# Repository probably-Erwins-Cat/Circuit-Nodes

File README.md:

# Circuit Nodes - Modular Electronics Building Blocks

Circuit Nodes is an educational tool shared under CC BY-NC-SA 4.0 to help students understand electronic circuits by physically building them.
Each module consists of a small PCB mounted on a 3D-printed base with puzzle-like notches, allowing users to create circuits in a grid-based structure. 
The PCBs include simple circuit elements such as resistors, capacitors, wire traces, switches, LEDs, lamps, and voltage or current measurement points, with their schematic representations printed directly on them. 
Magnetic connectors enable both physical attachment and electrical connection.

This system provides a low-cost entry point into electronics education while remaining scalable. 
By starting with basic components and expanding into more complex circuits, learners of all levels can benefit. 
The pedagogical value lies in reinforcing the connection between abstract circuit diagrams and tangible, working implementations, 
making theoretical concepts easier to grasp through hands-on experimentation.

---

## 📖 **[→ EXPLORE THE FULL DOCUMENTATION](https://probably-erwins-cat.github.io/Circuit-Nodes/)**

Complete guides, examples, research insights, and best practices are available in our **comprehensive GitHub Pages site**:

| Chapter | Link |
|---------|------|
| **Introduction** | https://probably-erwins-cat.github.io/Circuit-Nodes/introduction |
| **Getting Started** | https://probably-erwins-cat.github.io/Circuit-Nodes/getting-started |
| **Printable Bases** | https://probably-erwins-cat.github.io/Circuit-Nodes/printable-bases |
| **Assembly Instructions** | https://probably-erwins-cat.github.io/Circuit-Nodes/assembly-instructions |
| **Component Guide** | https://probably-erwins-cat.github.io/Circuit-Nodes/component-guide |
| **Sourcing & Manufacturing** | https://probably-erwins-cat.github.io/Circuit-Nodes/sourcing-manufacturing |
| **Getting Started** | https://probably-erwins-cat.github.io/Circuit-Nodes/getting-started |

# Features

*If you are an educator or represent a school interested in testing Circuit
Nodes, I can provide kits for evaluation and classroom use. Please reach out for
more details, see below*

-   Modular Design: 40x40mm PCBs mounted on 3D-printed bases with interlocking
    puzzle-like edges.
-   Hands-on Learning: Users assemble working circuits based on schematic
    diagrams.
-   Magnetic Connectors: Ensure secure physical and electrical connections.
-   Visual Representation: Each PCB features the corresponding circuit schematic
    for intuitive learning.
-   Expandable: Additional modules with more components can be designed and
    added.
-   Low Cost & Scalable: An affordable introduction to electronics that can be
    expanded as needed.

-   Pre-Assembled Kits Available: If the initial effort of manufacturing and
    assembling the components seems too high, I can provide ready-made circuit
    kits to make getting started easier.

# Getting Started, Assembly Instructions

- Refer to the repository contents below for a dedicated list and example circuits. 
- Plan what puzzle pieces you need and how many. An entry electronics kit for school settings needs less than 40 to cover most grounds.
- Download the necessary Gerber files for the circuits or kits you want to build from this repository.
- Manufacture the PCBs using your preferred(accessible) PCB fabrication service. 
  - Talk to the manufacturer if they can provide discounts for educational purpose. 
  - I recommend black background/solder mask and white silkscreen print. From my experience, this combination is the most durable combination.

-   **Decide which style of the 3D printable base you prefer for your scenario**:
    -  PCBs support screws of size M2, M2.3, and M2.6 self-tapping, as well as M2, M2.5 and M3 normal screws in combination with heat inserts.
        -   *Self-Tapping*: I recommend **M2 self-tapping and countersunk**
            screws. They provide the cleanest look, do not require additional
            assembly steps and auto-align the PCBs.
            Self-tapping screws, **can carve multiple threads when reinserting**, limited number of reuse of printable base.
        -   *Heat insert version*: Heat inserts provide **more durable and reliable way** for normal M2 and M2.5, 
            but requires time-consuming melting in the heat inserts with a solder iron or heat insert press.
    -   **Base Bottom Style**:
        -   The *magnetic bottom* base has highest build plate adhesion and allows for installing neodymium magnet, 
            so that the part can be attached to a magnetic surface. The internal height for components will be reduced by approx 3mm down to approx 16mm.
            **This makes a good teacher set for blackboards and whiteboards**
        -   The *skeletonized* one allows to look inside, but prevents curious
            fingers to get inside to accidentally break parts but allows exploring how
            components look in real life.
        -   The *open bottom* uses the least amount of material, is the fastest to
            print and, in case of a damaged component, the bottom side can be
            reached with a solder iron for *repair without disassembly*.            

-   **Before you go mass printing the base parts**, check which tolerance class,
    0.15mm and 0.2mm, suits your printer capabilities. 
    - The puzzle pieces should fit in together without a lot of wiggle room and without a lot of friction.
    - Smallest tolerance is preferred for best alignment of the parts.
-   Solder the component of the schematic of the PCB onto it first.
-   Assemble the puzzle pieces by placing the magnetic connectors in the pockets
    for the dedicated PCBs first. Slots without electrical connection stay     empty.
-   Place the PCB on top of the pins of the magnetic connectors and screw in
    four screws into the base. Screws should auto-center the PCB on the base.
-   Solder the magnetic connectors to the PCB.
-   Start building and experimenting with different circuit configurations!

You can also contact me for production and sale, I stock the puzzle pieces in my inventory and do quality checks including all other parts for assembly.

# Contributing

Contributions are welcome! Feel free to submit pull requests with new module
designs, improvements, or documentation updates. If you are a teacher and would
like to see specific schematics that align with your curriculum, but lack the
KiCAD skills to design them, I am happy to assist with the schematic design
process. Just reach out with your requirements, and I can help bring them to
life for your students.

Before submitting files, read [CONTRIBUTING.md](CONTRIBUTING.md). It explains
how contributed designs remain available for future Circuit Nodes kits while
contributors keep ownership of their work.

# Contact

For questions or collaboration, please open an discussion or reach out to me.

# DOI

# License

Circuit Nodes material is offered under **CC BY-NC-SA 4.0** (Creative Commons
Attribution-NonCommercial-ShareAlike 4.0 International) where the project holds
the necessary rights. You may use the design files to make your own Circuit
Nodes for noncommercial purposes. Schools may be able to commission ordinary
fabrication and assembly services for that use. The public license does not
permit use of licensed material primarily for commercial advantage. The project
creator retains the right to manufacture and sell products based on material
for which they hold the necessary rights. See
[LICENSING.md](LICENSING.md) for scope and
[LICENSE](LICENSE) for the full license.

---

## 📚 Citation & Research

This project is supported by peer-reviewed research published in **Physics Education**:

**Kubitschke, H., Hennig, F., Gleichmann, J., Schnauß, J., & Bitzenbauer, P. (2024).** 
*Modular 3D-printed Circuit Nodes for low-cost and hands-on Electricity Education.* 
Physics Education, 61(1), 015010.
**DOI**: [10.1088/1361-6552/ae1abd](https://doi.org/10.1088/1361-6552/ae1abd)

The paper includes:
- Educational design principles and cognitive load theory
- Technical specifications and cost analysis
- Teacher evaluation and feedback from 8 German secondary school physics teachers
- Learning outcome research and student perception studies

[Read the research publication](https://doi.org/10.1088/1361-6552/ae1abd) for detailed insights.

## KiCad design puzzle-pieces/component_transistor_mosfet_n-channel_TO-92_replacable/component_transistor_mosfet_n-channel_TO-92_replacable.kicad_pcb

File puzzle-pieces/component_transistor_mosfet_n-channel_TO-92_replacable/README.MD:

# Replaceable N-channel MOSFET (TO-92)

This node demonstrates how a gate voltage controls current through a transistor.

**The MOSFET is unprotected, but replaceable using the precision socket.** There is no built-in protection against incorrect connections, excessive gate voltage, or excessive current. The socket makes it easy to replace a damaged MOSFET or compare different types; it does not provide electrical protection.

## Connections and classroom use

| Terminal | Function |
| --- | --- |
| G: gate | Controls conduction through its voltage relative to the source |
| D: drain | Connects to the load; the other side of the load connects to the positive supply |
| S: source | Connects to the supply return in a low-side switching experiment |

At approximately zero gate-to-source voltage, the transistor is off in the normal drain-to-source direction. Increasing gate voltage allows current to flow. **Threshold voltage marks the beginning of conduction, not full turn-on.** These parts are useful for small-load experiments around a 5 V gate drive; do not assume reliable full turn-on at 3.3 V.

- Measure load current as gate voltage changes.
- Compare voltage-driven gate control with the base current of an NPN transistor.
- Observe that a disconnected gate can retain charge. An external gate-to-source pull-down resistor, for example 100 kΩ, gives a defined off state.
- Investigate the internal body diode: an off MOSFET does not block current equally in both directions.

## Suggested parts and usage

The three contacts have 2.54 mm spacing. Solder a precision socket onto the diagram side and plug the MOSFET into it, as shown above. This allows a damaged MOSFET to be replaced or different types to be compared. A matching MOSFET can also be soldered directly into the same pads.

Use a TO-92 MOSFET with **1 = source, 2 = gate, 3 = drain (S-G-D)**. Wide in-line leads fit the socket pitch; closely spaced leads can be gently spread beforehand.

| MOSFET | Maximum drain-source voltage | Pin order, flat face toward you and leads pointing down |
| --- | --- | --- |
| 2N7000 | 60 V | S-G-D |
| TN0606N3-G | 60 V | S-G-D |
| VN0106N3-G | 60 V | S-G-D |
| TN0610N3-G | 100 V | S-G-D |
| VN10KN3-G | 60 V | S-G-D |

These are pin-compatible options, but their switching characteristics and current limits differ. Check the exact manufacturer's datasheet before fitting a replacement. The drain-source rating is not the permissible gate voltage.

**Insert the MOSFET with each lead connected to the corresponding S, G, or D terminal.** Disconnect power before replacing it.

## Practical notes

This node has no built-in gate protection, pull-down resistor, load-current limiter, or flyback diode. Use an external resistor/current limit for the load and a flyback diode for inductive loads.

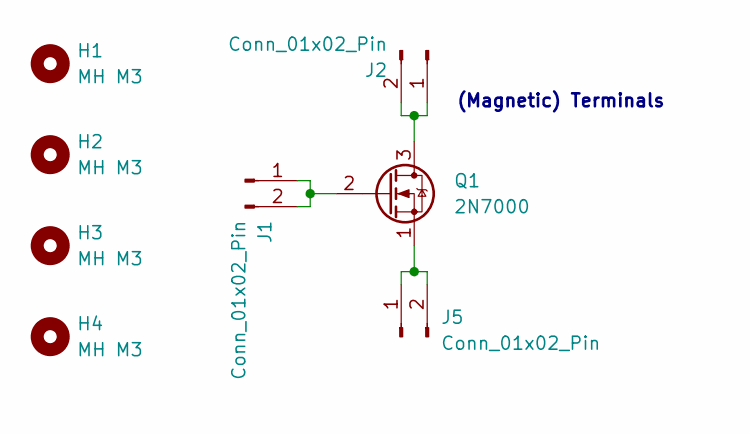
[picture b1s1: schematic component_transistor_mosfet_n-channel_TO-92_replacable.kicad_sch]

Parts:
H1, H2, H3, H4: MH M3; MountingHole_3.0mm_M3_tight
J1, J2, J5: Conn_01x02_Pin; Magnetic_Connector_1x02_P2.5mm_Horizontal_round-ears
Q1: 2N7000; HDR-TH_3P-P2.54-V-F-3

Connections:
Leitung1: J5.1, J5.2, Q1.1 (S)
unnamed: J1.1, J1.2, Q1.2 (G)
unnamed: J2.1, J2.2, Q1.3 (D)

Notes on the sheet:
(Magnetic) Terminals

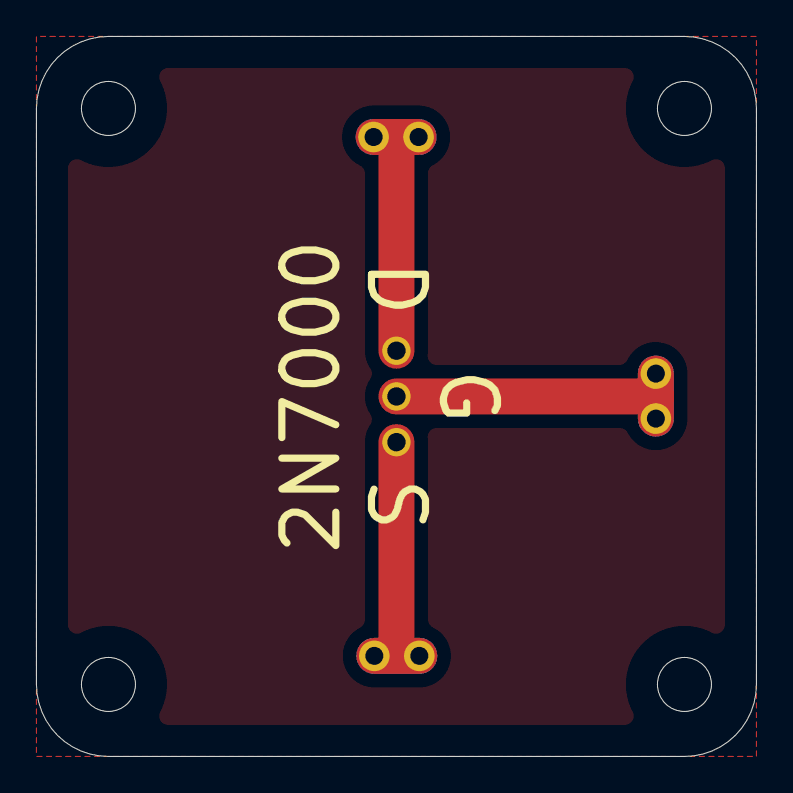
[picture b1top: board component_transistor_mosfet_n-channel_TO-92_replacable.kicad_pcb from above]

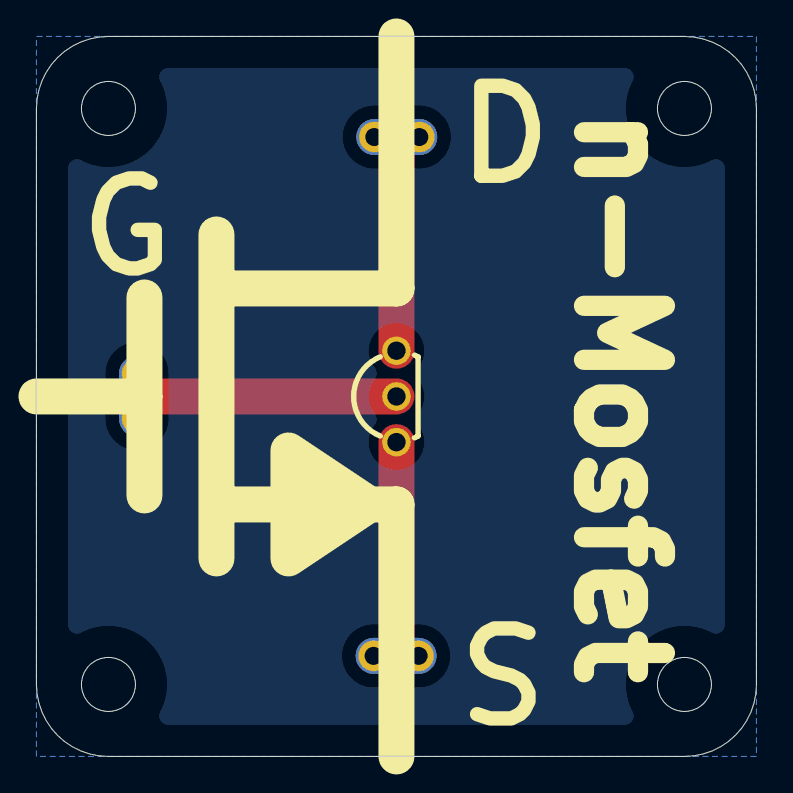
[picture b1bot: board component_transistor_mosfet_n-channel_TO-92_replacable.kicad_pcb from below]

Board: 2 copper layers, 40.0 x 40.0 mm, 8 parts (5 on the bottom side), 3 nets.

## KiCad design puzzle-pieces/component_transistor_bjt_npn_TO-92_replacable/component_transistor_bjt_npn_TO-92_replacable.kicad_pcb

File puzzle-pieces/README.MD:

# Circuit Nodes Puzzle Pieces

All Circuit Nodes puzzle pieces are collected and constantly updated here. Each piece represents a specific circuit component or connection type, named according to their schematic symbols rather than specific component numbers. For example, the folder for an n-channel MOSFET will contain compatible part numbers like the 2N7000.

## Design Standard

All puzzle pieces follow a consistent design template to ensure they work together seamlessly:

- **Physical dimensions**: 40×40 mm square outline with 4 mm radius corners
- **Mounting**: Four M3-compatible screw holes in the corners (2.9–3.0 mm diameter, 4 mm from edges)
- **Visual style**: 2 mm thick pictogram lines with rounded edges where possible
- **Electrical layout**: Copper pour kept at least 2 mm from board edges and not connected to GND or power supply
- **Connector interface**: Integrated magnetic pogo connectors (see the dedicated pogo-connector folder)

## Board-to-Board Connectors

All pieces are designed for integrated magnetic pogo connectors. The layout and spacing of each puzzle piece are carefully matched to these connectors for reliable, automatic alignment when pieces are joined.

## Complete Catalog

| Name | Image |
|------|-------|
| [breadboard_grid-2.54mm_1x1](breadboard_grid-2.54mm_1x1) |  |
| [breadboard_grid-2.54mm_1x2](breadboard_grid-2.54mm_1x2) |  |
| [breadboard_grid-2.54mm_2x2](breadboard_grid-2.54mm_2x2) |  |
| [component_capacitor-polarized_ruggedized](component_capacitor-polarized_ruggedized) |  |
| [component_capacitor-polarized_ruggedized_replacable](component_capacitor-polarized_ruggedized_replacable) |  |
| [component_capacitor-unpolarized-MLCC_SMT](component_capacitor-unpolarized-MLCC_SMT) |  |
| [component_charge-pump-inverter](component_charge-pump-inverter) |  |
| [component_diode_general_silicon](component_diode_general_silicon) |  |
| [component_diode_zener](component_diode_zener) |  |
| [component_fuse-PolyFuse](component_fuse-PolyFuse) |  |
| [component_inductance_THT](component_inductance_THT) |  |
| [component_lamp-E10_screw-socket](component_lamp-E10_screw-socket) |  |
| [component_lamp-E10_THT](component_lamp-E10_THT) |  |
| [component_lamp-LED-module_ruggedized](component_lamp-LED-module_ruggedized) |  |
| [component_LED_replacable](component_LED_replacable) |  |
| [component_LED_THT](component_LED_THT) |  |
| [component_motor-with-propeller](component_motor-with-propeller) |  |
| [component_potentiometer_high-power](component_potentiometer_high-power) |  |
| [component_potentiometer_slider_screw-mounted](component_potentiometer_slider_screw-mounted) |  |
| [component_potentiometer_slider_THT](component_potentiometer_slider_THT) |  |
| [component_resistor_SMT](component_resistor_SMT) |  |
| [component_resistor_SMT_top-mount](component_resistor_SMT_top-mount) |  |
| [component_resistor_SMT_with-printed-value](component_resistor_SMT_with-printed-value) |  |
| [component_resistor_THT_3W](component_resistor_THT_3W) |  |
| [component_resistor_THT_3W_with-printed-value](component_resistor_THT_3W_with-printed-value) |  |
| [component_switch-micro-Normally-Closed_THT](component_switch-micro-Normally-Closed_THT) |  |
| [component_switch-micro-Normally-Open_THT](component_switch-micro-Normally-Open_THT) |  |
| [component_switch-On-OFF_THT](component_switch-On-OFF_THT) |  |
| [component_switch-On1-OFF-On2_THT](component_switch-On1-OFF-On2_THT) |  |
| [component_switch-On1-On2_THT](component_switch-On1-On2_THT) |  |
| [component_switch-tactile-Normally-Open_THT](component_switch-tactile-Normally-Open_THT) |  |
| [component_transistor_bjt_npn_TO-92_replacable](component_transistor_bjt_npn_TO-92_replacable) |  |
| [component_transistor_mosfet_n-channel_ruggedized](component_transistor_mosfet_n-channel_ruggedized) |  |
| [component_transistor_mosfet_n-channel_TO-92_replacable](component_transistor_mosfet_n-channel_TO-92_replacable) |  |
| [end-node-double_AC](end-node-double_AC) |  |
| [end-node-double_blank](end-node-double_blank) |  |
| [end-node-double_current](end-node-double_current) |  |
| [end-node-double_plus-minus](end-node-double_plus-minus) |  |
| [end-node-double_plus-minus_with-protection](end-node-double_plus-minus_with-protection) |  |
| [end-node-double_plus-minus_with-USB-PD](end-node-double_plus-minus_with-USB-PD) |  |
| [end-node-single_blank](end-node-single_blank) |  |
| [end-node-single_minus](end-node-single_minus) |  |
| [end-node-single_plus](end-node-single_plus) |  |
| [wire-angle_blank](wire-angle_blank) |  |
| [wire-angle_node-voltage](wire-angle_node-voltage) |  |
| [wire-bridge_blank](wire-bridge_blank) |  |
| [wire-straight_blank](wire-straight_blank) |  |
| [wire-straight_node-voltage](wire-straight_node-voltage) |  |
| [wire-T-crossing_blank](wire-T-crossing_blank) |  |
| [wire-T-crossing_node-voltage](wire-T-crossing_node-voltage) |  |
| [wire-two-angles_blank](wire-two-angles_blank) |  |
| [wire-X-crossing_blank](wire-X-crossing_blank) |  |
| [wire-X-crossing_node-voltage](wire-X-crossing_node-voltage) |  |

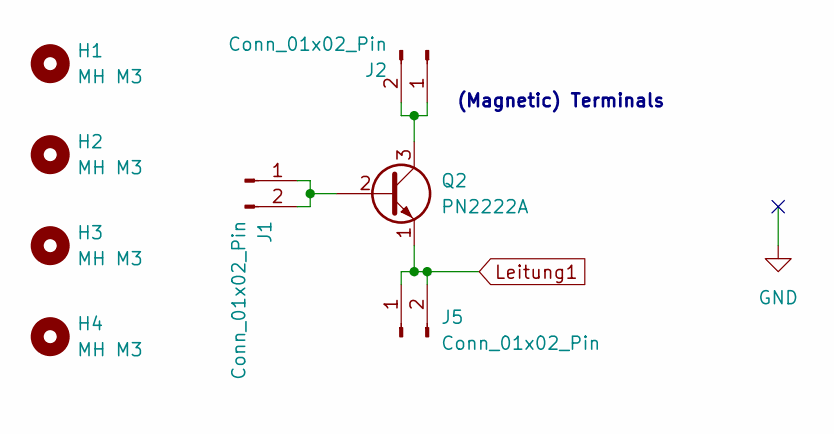
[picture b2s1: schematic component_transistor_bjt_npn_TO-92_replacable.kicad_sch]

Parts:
H1, H2, H3, H4: MH M3; MountingHole_3.0mm_M3_tight
J1, J2, J5: Conn_01x02_Pin; Magnetic_Connector_1x02_P2.5mm_Horizontal_round-ears
Q2: PN2222A; HDR-TH_3P-P2.54-V-F-3

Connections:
Leitung1: J5.1, J5.2, Q2.1 (E)
unnamed: J1.1, J1.2, Q2.2 (B)
unnamed: J2.1, J2.2, Q2.3 (C)

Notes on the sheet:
(Magnetic) Terminals

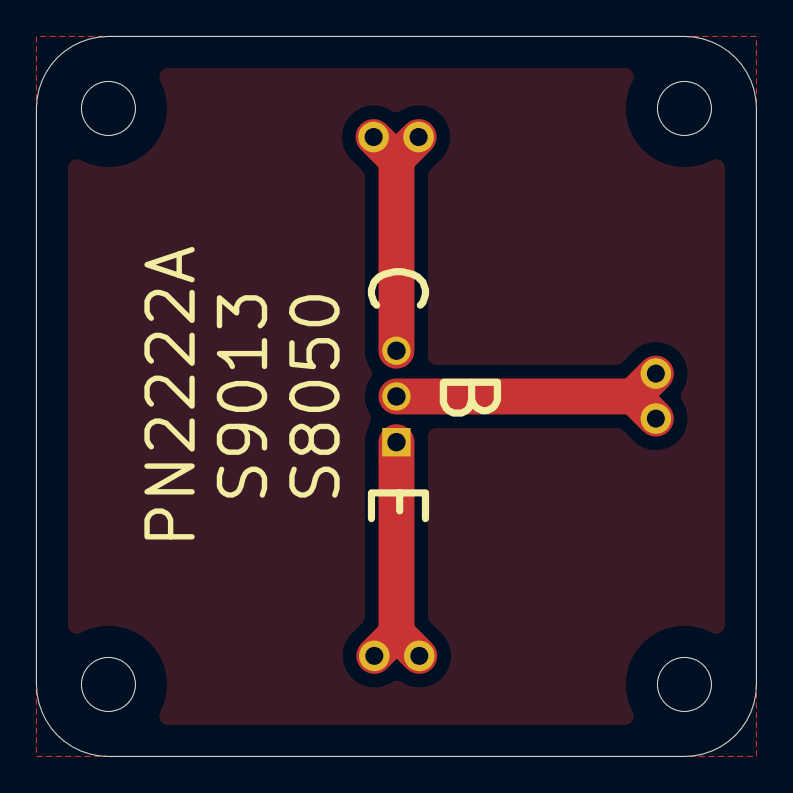
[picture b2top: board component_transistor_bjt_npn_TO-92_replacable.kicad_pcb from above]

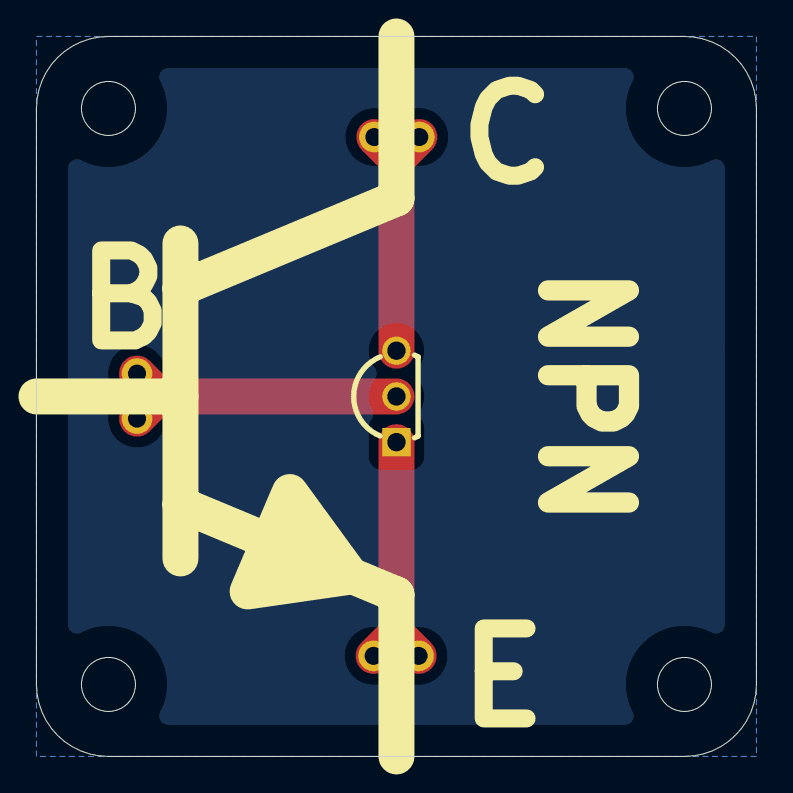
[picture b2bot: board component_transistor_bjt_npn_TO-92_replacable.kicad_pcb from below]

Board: 2 copper layers, 40.0 x 40.0 mm, 8 parts (5 on the bottom side), 3 nets.

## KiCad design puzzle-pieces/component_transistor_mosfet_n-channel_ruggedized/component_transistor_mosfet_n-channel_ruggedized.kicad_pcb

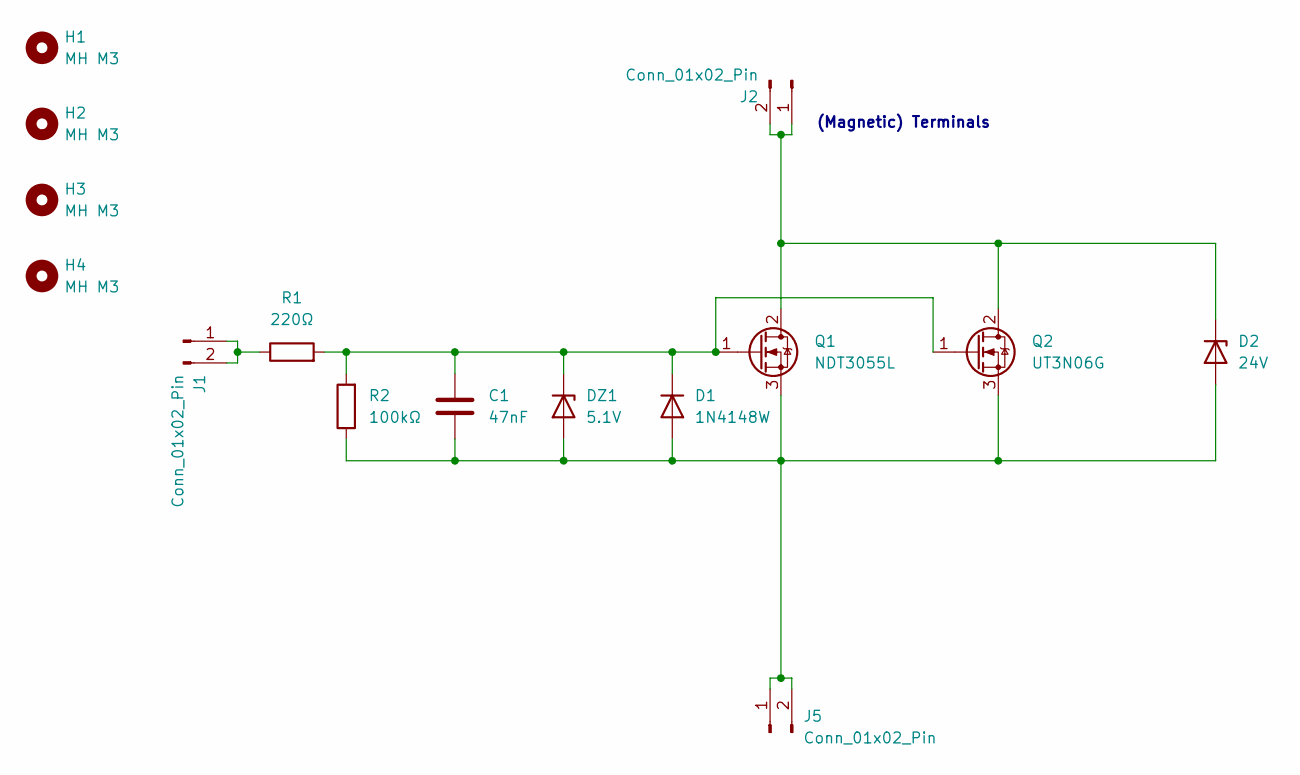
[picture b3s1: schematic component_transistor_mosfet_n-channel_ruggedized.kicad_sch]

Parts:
C1: 47nF; C_1206_3216Metric_Pad1.33x1.80mm_HandSolder; LCSC C303962
D1: 1N4148W; Nexperia_CFP3_SOD-123W; LCSC C81598
D2: 24V; D_SMA; LCSC C155317
DZ1: 5.1V; Nexperia_CFP3_SOD-123W; LCSC C2827905
H1, H2, H3, H4: MH M3; MountingHole_3.0mm_M3_tight
J1, J2, J5: Conn_01x02_Pin; Magnetic_Connector_1x02_P2.5mm_Horizontal_round-ears
Q1: NDT3055L; SOT-223-3_TabPin2; LCSC C5354979
Q2: UT3N06G; SOT-89-3_Handsoldering; LCSC C127044
R1: 220Ω; R_1206_3216Metric_Pad1.30x1.75mm_HandSolder; LCSC C17957
R2: 100kΩ; R_1206_3216Metric_Pad1.30x1.75mm_HandSolder; LCSC C17900

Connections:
unnamed: C1.2, D1.2 (A), D2.2 (A), DZ1.2 (A), J5.1, J5.2, Q1.3 (S), Q2.3 (S), R2.1
unnamed: C1.1, D1.1 (K), DZ1.1 (K), Q1.1 (G), Q2.1 (G), R1.2, R2.2
unnamed: D2.1 (K), J2.1, J2.2, Q1.2 (D), Q2.2 (D)
unnamed: J1.1, J1.2, R1.1

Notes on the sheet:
(Magnetic) Terminals

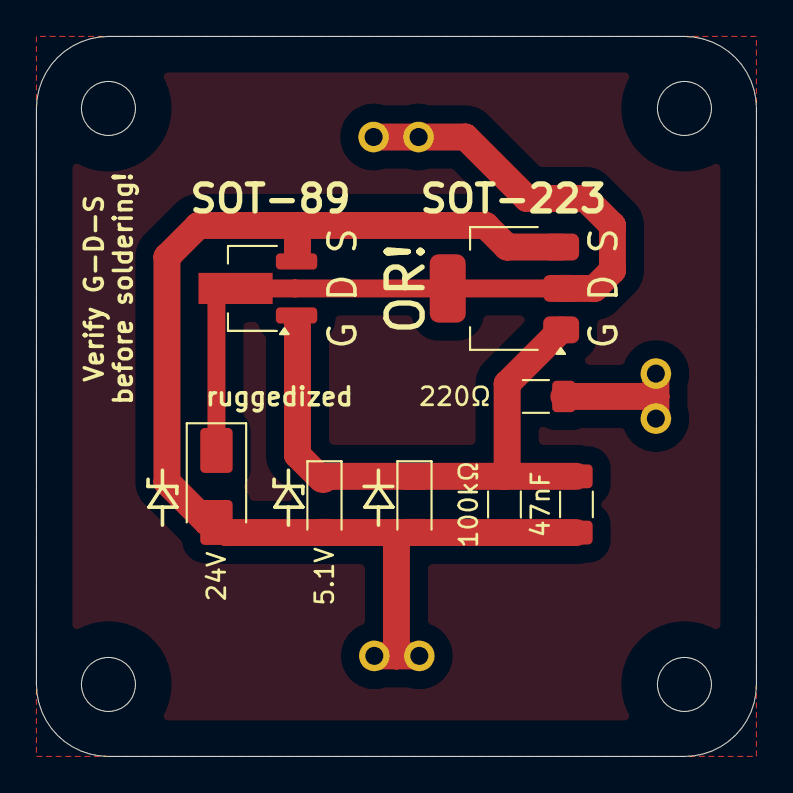
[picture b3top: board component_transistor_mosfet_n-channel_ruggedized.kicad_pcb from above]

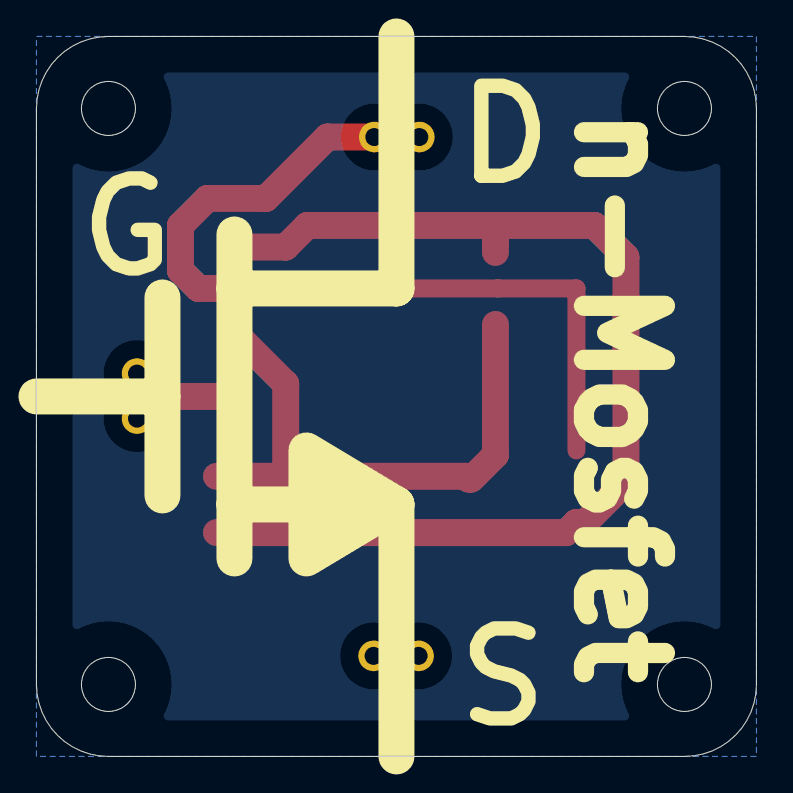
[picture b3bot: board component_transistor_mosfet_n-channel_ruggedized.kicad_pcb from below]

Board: 2 copper layers, 40.0 x 40.0 mm, 15 parts (4 on the bottom side), 4 nets.

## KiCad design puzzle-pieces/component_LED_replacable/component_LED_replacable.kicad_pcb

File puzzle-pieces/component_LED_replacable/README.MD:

# Replaceable LED

This node holds a plug-in LED that can be replaced without soldering. Students can compare LED colors, observe one-way conduction, and investigate the relationship between current and brightness.

## Classroom experiments

- Compare the forward voltage of LEDs of different colors at the same current.
- Change the external series resistor to observe how current affects brightness.
- Reverse the connection to demonstrate polarity dependence, keeping reverse voltage within the LED's rating.

## Connection and replacement

Insert the LED according to the printed polarity markings. The flat side of a conventional round LED usually identifies the cathode; check the selected LED's datasheet, especially after its leads have been shortened. Disconnect the supply before replacing it, and support the socket while inserting or removing leads.

**Use an external series resistor or a suitable current-limited source. This node has no built-in current limiting or reverse-voltage protection.** Its replaceable LED can be damaged by excessive current or reverse voltage.

Choose the resistor using:

`R = (V_supply − V_forward) / I_LED`

Forward voltage depends on LED color, current, and temperature. Choose the current and resistor power rating for the fitted LED; do not connect it directly across a supply.

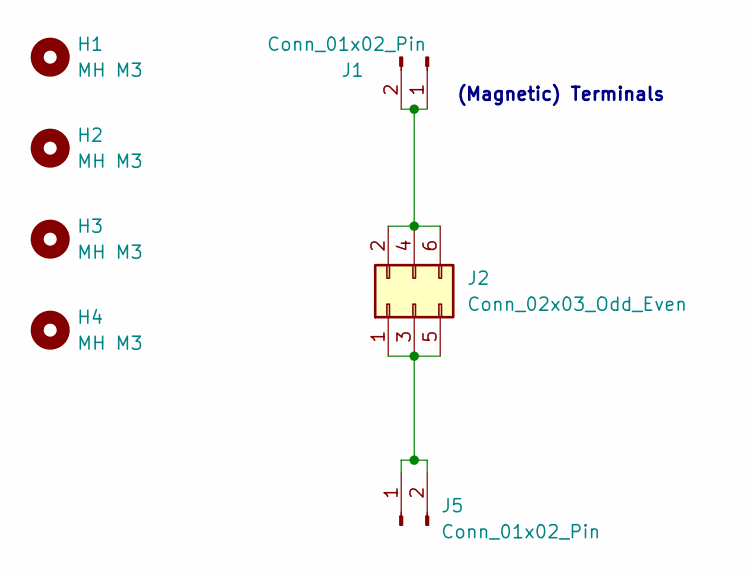
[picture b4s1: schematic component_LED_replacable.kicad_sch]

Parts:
H1, H2, H3, H4: MH M3; MountingHole_3.0mm_M3_tight
J1, J5: Conn_01x02_Pin; Magnetic_Connector_1x02_P2.5mm_Horizontal_round-ears
J2: Conn_02x03_Odd_Even; CONN-SMD_HC-PM254-5.0H-2X3PS-02A

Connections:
unnamed: J1.1, J1.2, J2.2, J2.4, J2.6
unnamed: J2.1, J2.3, J2.5, J5.1, J5.2

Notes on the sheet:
(Magnetic) Terminals

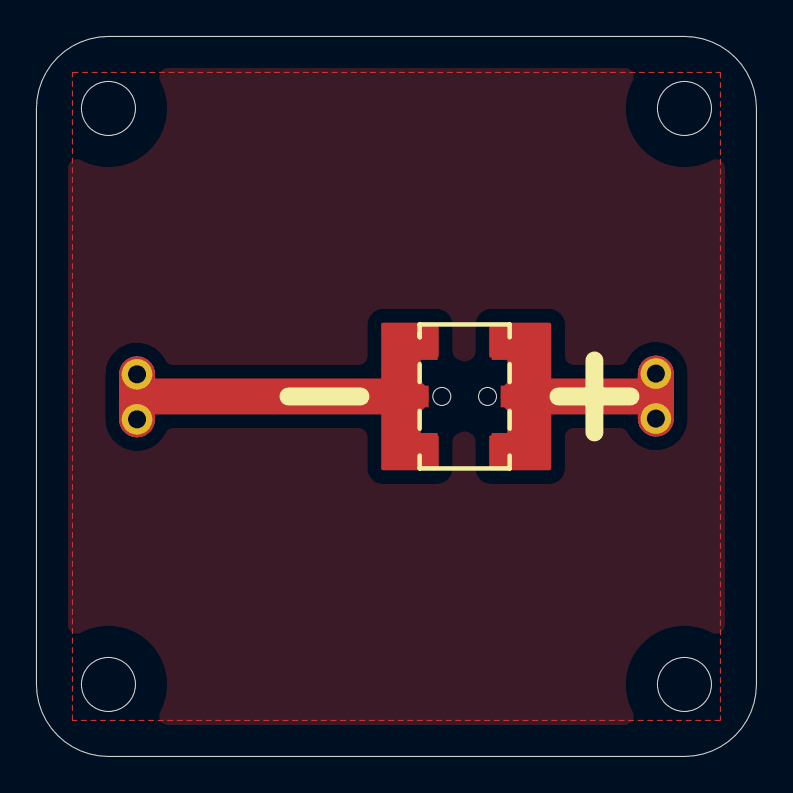
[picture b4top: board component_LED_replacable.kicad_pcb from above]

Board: 2 copper layers, 40.0 x 40.0 mm, 7 parts (0 on the bottom side), 2 nets.

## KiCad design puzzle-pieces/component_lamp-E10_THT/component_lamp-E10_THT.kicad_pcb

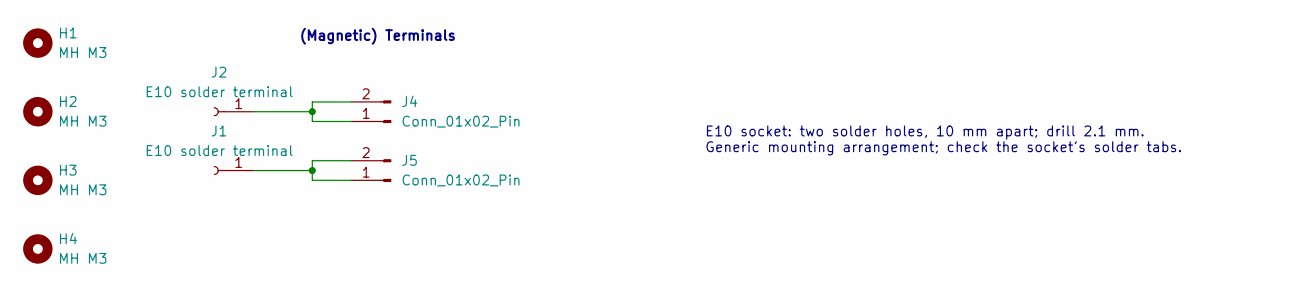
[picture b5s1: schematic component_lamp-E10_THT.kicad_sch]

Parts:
H1, H2, H3, H4: MH M3; MountingHole_3.0mm_M3_tight
J1, J2: E10 solder terminal; SolderHole_D2.1mm_OD3.9mm
J4, J5: Conn_01x02_Pin; Magnetic_Connector_1x02_P2.5mm_Horizontal_round-ears

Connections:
unnamed: J1.1, J5.1, J5.2
unnamed: J2.1, J4.1, J4.2

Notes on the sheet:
(Magnetic) Terminals
E10 socket: two solder holes, 10 mm apart; drill 2.1 mm. Generic mounting arrangement; check the socket's solder tabs.

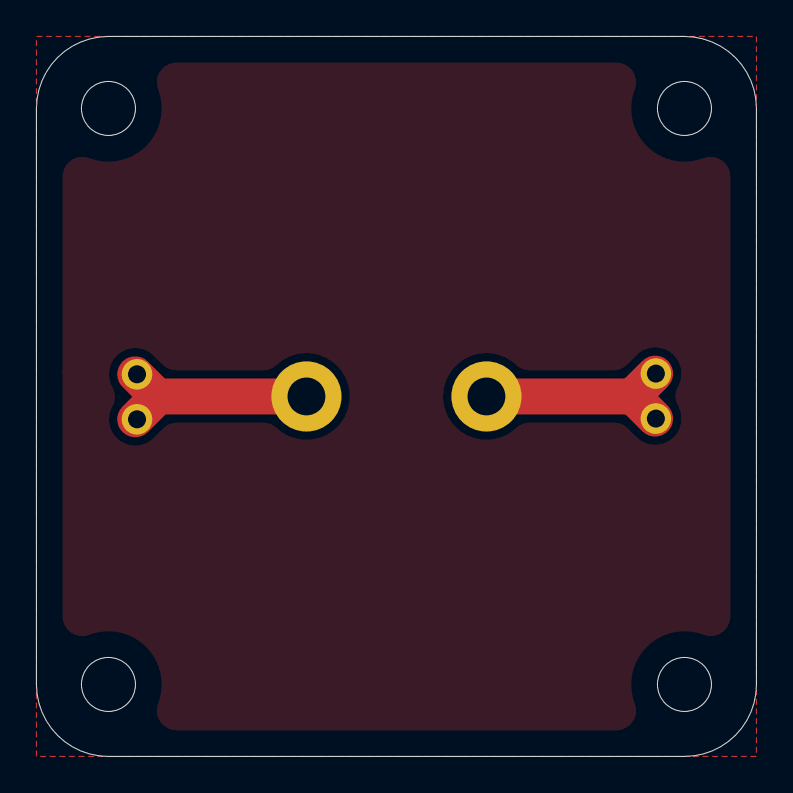
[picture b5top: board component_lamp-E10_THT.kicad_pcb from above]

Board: 2 copper layers, 40.0 x 40.0 mm, 8 parts (0 on the bottom side), 2 nets.

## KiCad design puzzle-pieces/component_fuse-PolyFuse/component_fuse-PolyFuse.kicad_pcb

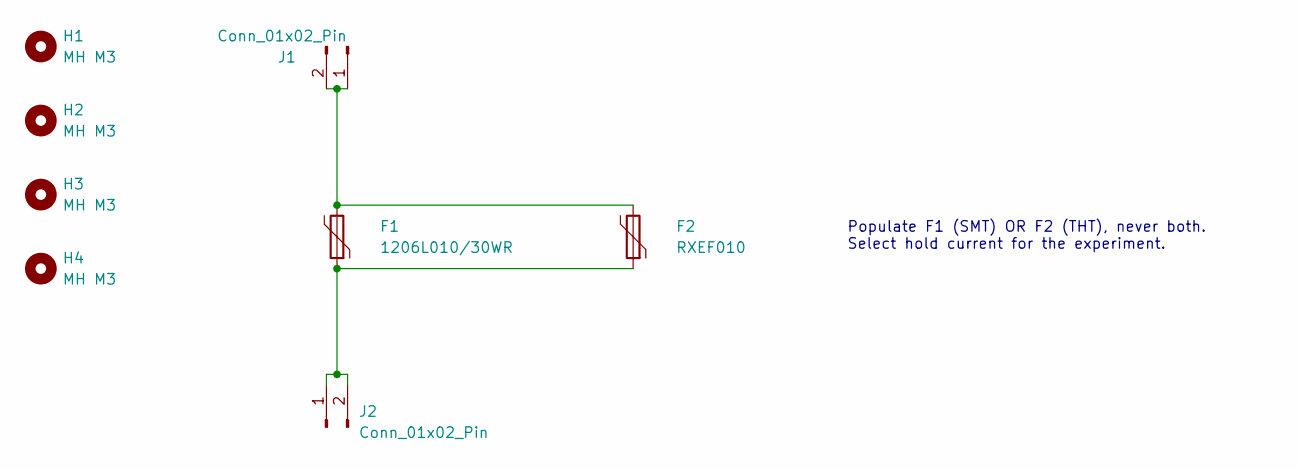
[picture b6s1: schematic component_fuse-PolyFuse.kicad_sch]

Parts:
F1: 1206L010/30WR; R_1206_3216Metric_Pad1.30x1.75mm_HandSolder; LCSC C2153988
F2: RXEF010; Fuse_Bourns_MF-RHT050; LCSC C5392
H1, H2, H3, H4: MH M3; MountingHole_3.2mm_M3
J1, J2: Conn_01x02_Pin; Magnetic_Connector_1x02_P2.5mm_Horizontal_round-ears

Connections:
unnamed: F1.2, F2.2, J1.1, J1.2
unnamed: F1.1, F2.1, J2.1, J2.2

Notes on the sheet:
Populate F1 (SMT) OR F2 (THT), never both. Select hold current for the experiment.

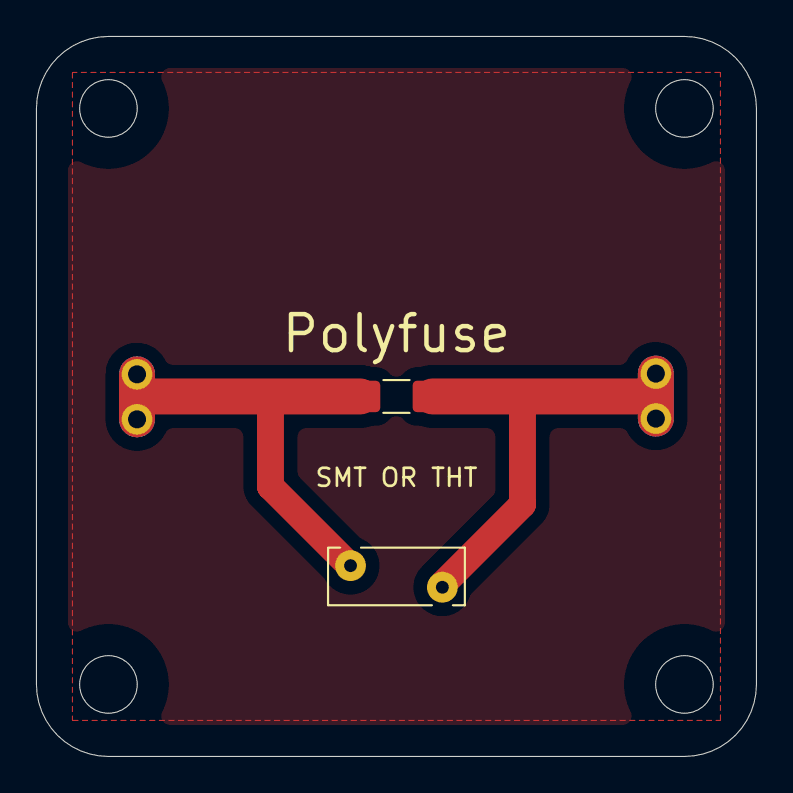
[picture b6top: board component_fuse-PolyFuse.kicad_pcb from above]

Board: 2 copper layers, 40.0 x 40.0 mm, 8 parts (0 on the bottom side), 2 nets.

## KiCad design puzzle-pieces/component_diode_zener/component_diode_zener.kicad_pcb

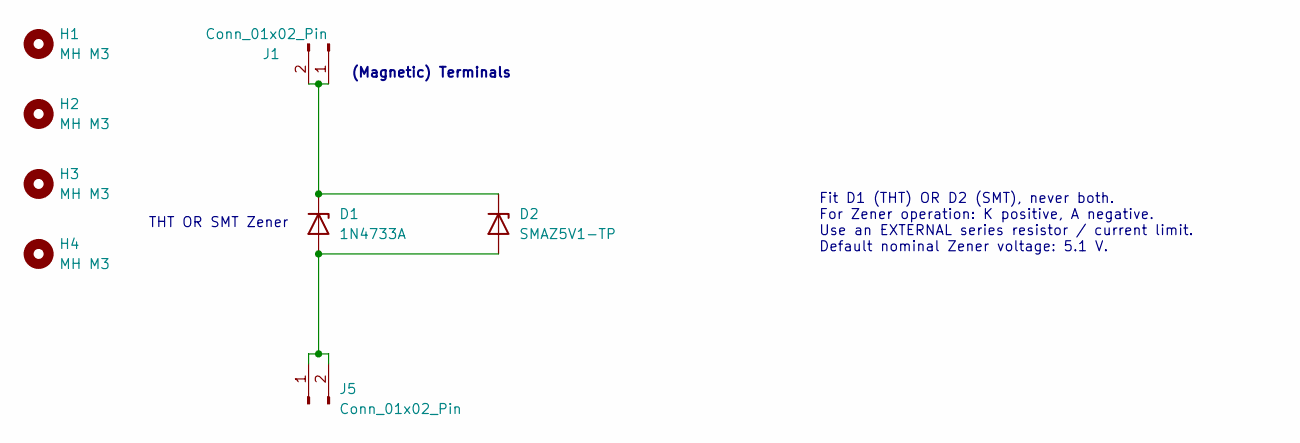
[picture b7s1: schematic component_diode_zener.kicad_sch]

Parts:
D1: 1N4733A; D_DO-15_P12.70mm_Horizontal; LCSC C5157516
D2: SMAZ5V1-TP; D_SMA-SMB_Universal_Handsoldering; LCSC C49274882
H1, H2, H3, H4: MH M3; MountingHole_3.0mm_M3_tight
J1, J5: Conn_01x02_Pin; Magnetic_Connector_1x02_P2.5mm_Horizontal_round-ears

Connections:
unnamed: D1.2 (A), D2.2 (A), J5.1, J5.2
unnamed: D1.1 (K), D2.1 (K), J1.1, J1.2

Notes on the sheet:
(Magnetic) Terminals
THT OR SMT Zener
Fit D1 (THT) OR D2 (SMT), never both. For Zener operation: K positive, A negative. Use an EXTERNAL series resistor / current limit. Default nominal Zener voltage: 5.1 V.

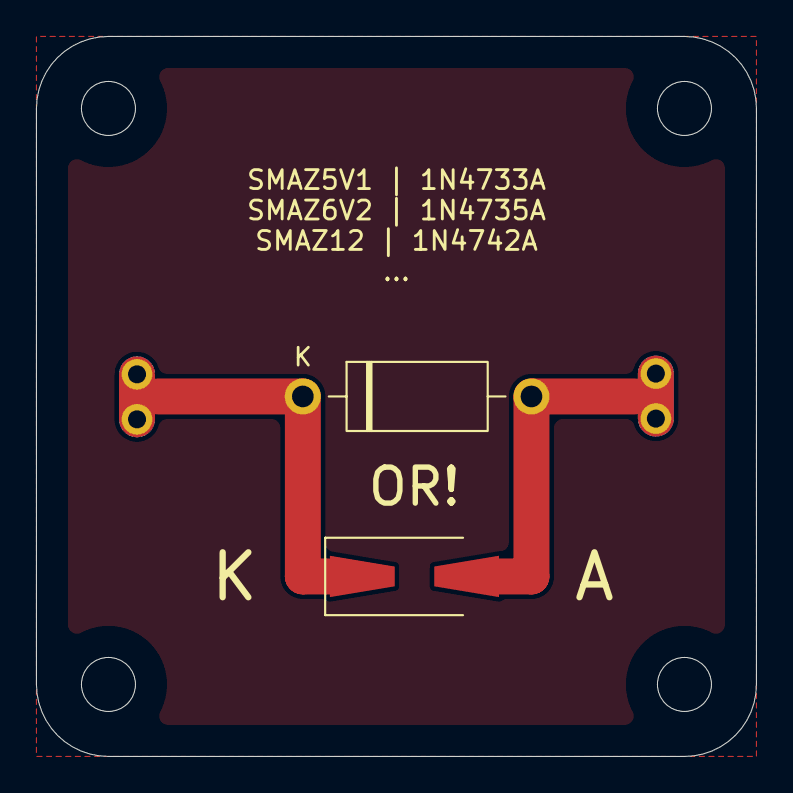
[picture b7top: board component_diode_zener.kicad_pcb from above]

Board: 2 copper layers, 40.0 x 40.0 mm, 8 parts (0 on the bottom side), 2 nets.

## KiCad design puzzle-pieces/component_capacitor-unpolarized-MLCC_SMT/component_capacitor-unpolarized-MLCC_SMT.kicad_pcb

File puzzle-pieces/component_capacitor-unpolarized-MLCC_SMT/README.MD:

# Unpolarized capacitor (MLCC SMT)

This node uses parallel multilayer ceramic capacitors (MLCCs) for charge storage, filtering, and RC or "slow AC" experiments. Either terminal can be positive.

## Capacitance and assembly

The silkscreen specifies **1206, 10–22 µF, 25 V** capacitors. There are 25 parallel positions; populate fewer positions if less capacitance is needed. Empty capacitor positions require no bridges.
The footprints allow hand soldering, but a stencil and reflow process make a fully populated bank much easier to assemble. Fewer populated positions also reduce manual work.

| Population | Nominal total capacitance |
| --- | --- |
| 25 × 10 µF | 250 µF |
| 25 × 22 µF | 550 µF |

## Series resistor: 0–10 Ω

R1 is marked **0–10 Ω**. **10 Ω is the default** to limit connection and charging-current peaks. This resistor does not provide complete fault protection, only current limiting

Fit a **0 Ω link** when bypassing the resistor is appropriate for the experiment, with current limiting provided elsewhere. Leaving R1 unpopulated disconnects the capacitor bank.

For the nominal 550 µF bank, capacitive reactance is approximately 300 Ω at 1 Hz and 3 kΩ at 0.1 Hz. A 10 Ω series resistor therefore has little influence on slow sinusoidal experiments. Abrupt square-wave transitions can still cause current peaks.

## Bleeder resistor: 1 MΩ or greater

R2 is marked **1 MΩ+**, meaning a bleeder resistance of **1 MΩ or greater**. 

Choose the fitted resistance to balance discharge time against loading of the experiment. With the nominal 550 µF bank, the resistor-only time constant `τ = RC` is about **550 seconds at 1 MΩ** or **5,500 seconds at 10 MΩ**. These are gradual discharge paths, not immediate discharge. The capacitors and TVS have also tiny internal leaking paths, so the effective bleed resistance is likely approx. 0.5–2 MΩ.

## Transient protection and operating notes

D1, marked **TVS**, is the bidirectional ESD protection device , e.g. Nexperia **PESD1IVN24-A**. It suppresses brief transients; it is not a regulator or protection against sustained overvoltage.

Use voltages within the ratings of the fitted parts and limit source current. Disconnect the supply and check the terminal voltage before changing connections or handling the board. Avoid shorting the charged bank.

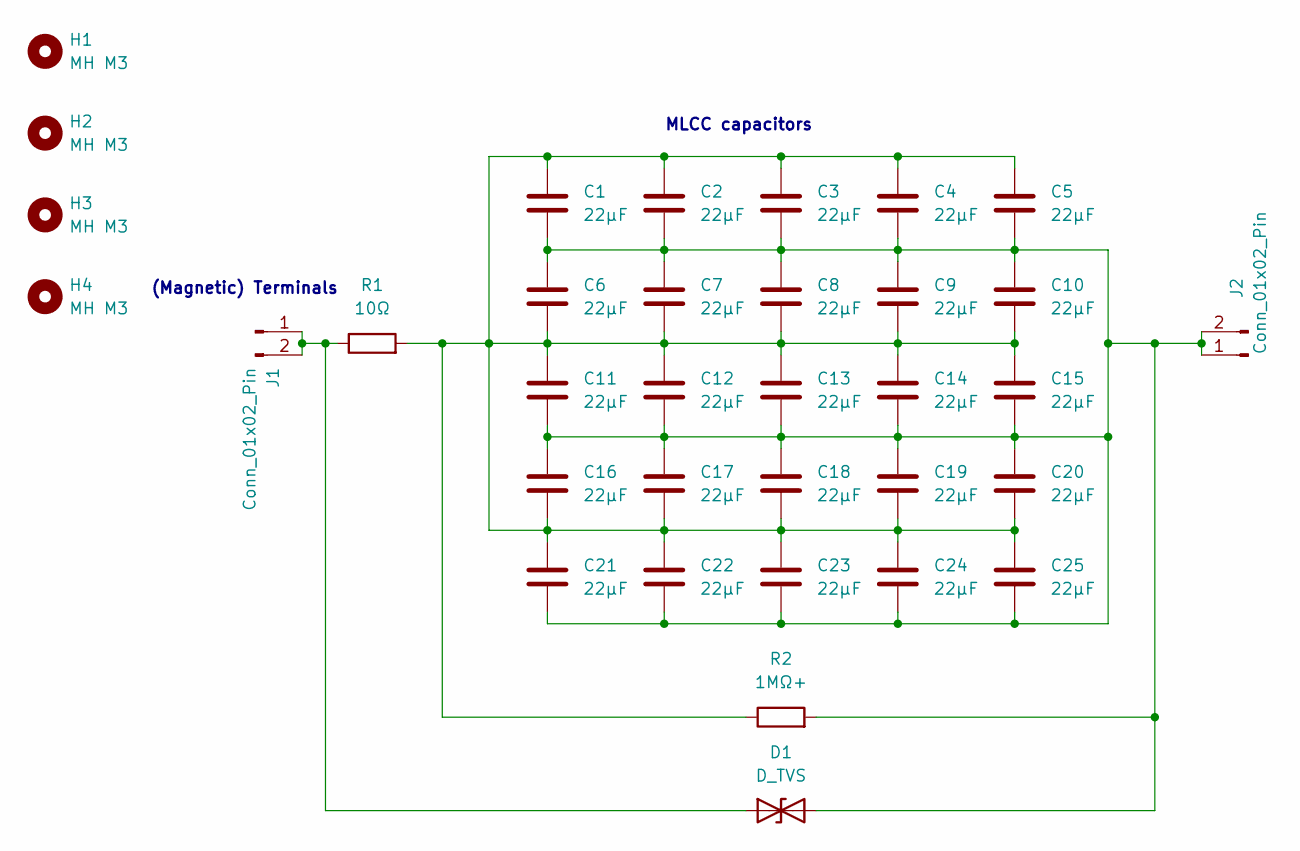
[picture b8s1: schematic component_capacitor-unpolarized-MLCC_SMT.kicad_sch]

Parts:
C1, C2, C3, C4, C5, C6, C7, C8, C9, C10, C11, C12, C13, C14, C15, C16, C17, C18, C19, C20, C21, C22, C23, C24, C25: 22µF; C_1206_3216Metric_Pad1.33x1.80mm_HandSolder; LCSC C12891
D1: D_TVS; D_SOD-323_HandSoldering; LCSC C503381
H1, H2, H3, H4: MH M3; MountingHole_3.0mm_M3_tight
J1, J2: Conn_01x02_Pin; Magnetic_Connector_1x02_P2.5mm_Horizontal_round-ears
R1: 10Ω; R_1206_3216Metric_Pad1.30x1.75mm_HandSolder; LCSC C17903
R2: 1MΩ+; R_1206_3216Metric_Pad1.30x1.75mm_HandSolder; LCSC C26119

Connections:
unnamed: C1.1, C2.1, C3.1, C4.1, C5.1, C6.2, C7.2, C8.2, C9.2, C10.2, C11.1, C12.1, C13.1, C14.1, C15.1, C16.2, C17.2, C18.2, C19.2, C20.2, C21.1, C22.1, C23.1, C24.1, C25.1, R1.2, R2.1
unnamed: D1.1 (A1), J1.1, J1.2, R1.1
unnamed: C1.2, C2.2, C3.2, C4.2, C5.2, C6.1, C7.1, C8.1, C9.1, C10.1, C11.2, C12.2, C13.2, C14.2, C15.2, C16.1, C17.1, C18.1, C19.1, C20.1, C21.2, C22.2, C23.2, C24.2, C25.2, D1.2 (A2), J2.1, J2.2, R2.2

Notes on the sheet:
(Magnetic) Terminals
MLCC capacitors

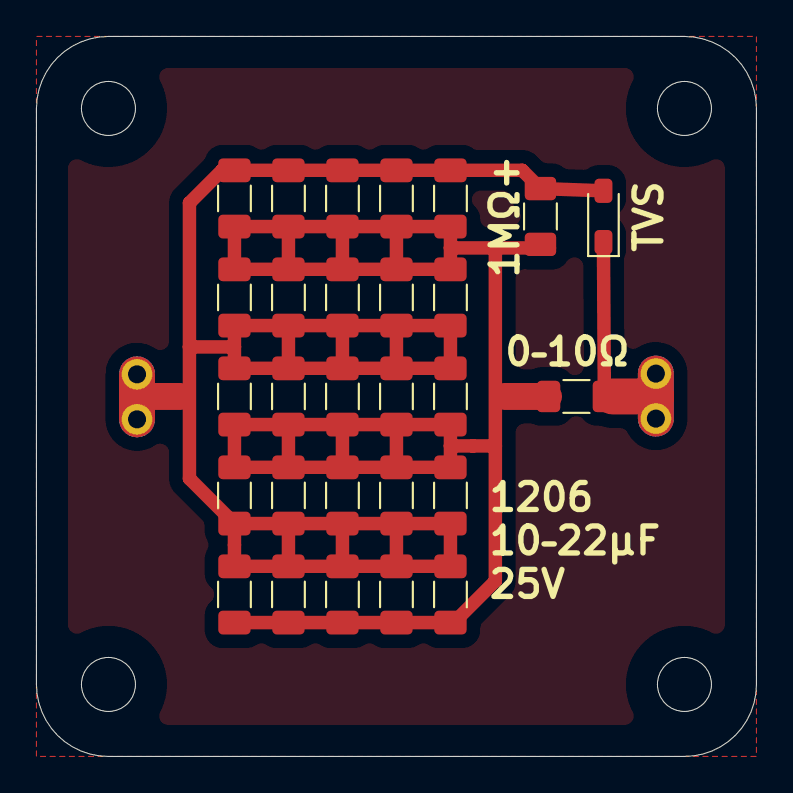
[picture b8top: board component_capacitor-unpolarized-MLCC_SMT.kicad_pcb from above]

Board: 2 copper layers, 40.0 x 40.0 mm, 34 parts (0 on the bottom side), 3 nets.

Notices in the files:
parts and their libraries:
Samtec SL-103-T-19; CADENAS; CC BY-ND 4.0; https://www.samtec.com/products/sl-103-t-19
